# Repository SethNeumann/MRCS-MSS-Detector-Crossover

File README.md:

# Modular Signaling System Crossover board cpOD-M
## License: CERN Open Hardware Licence v1.2

This Barry Draper design conforms to the 
[Modular Signaling System](http://modularsignalsystem.info/index.html)
(MSS) standard, first described by Greg Fuhriman in RMJ in the
1990s, as well as the proposed MSS 2.0 standard.  MSS is widely
used in the Free-mo world, but its also a great solution for a
layout needing basic ABS signaling.  A Crossover board is for a
non-signaled module (detection only).  The MSS Detector Crossover
Board includes a power supply that is fed by the Free-mo Aux Bus
(12 to 14 Volt AC or DCC) and has connectors to communicate with
two adjacent modules and a socket for current detector such as a
[cpOD-M](http://www.modelrailroadcontrolsystems.com/cpod-control-point-occupancy-detector/)
or Dr. Chubb's
[DCCOD](https://www.jlcenterprises.net/products/dcc-optimized-detector).
The MSS Crossover, a cpOD-M, and two straight-through network cables
are all you need to add signal detection to a single track Free-mo
module. (As expected, two of each would be needed for a double track
module.)

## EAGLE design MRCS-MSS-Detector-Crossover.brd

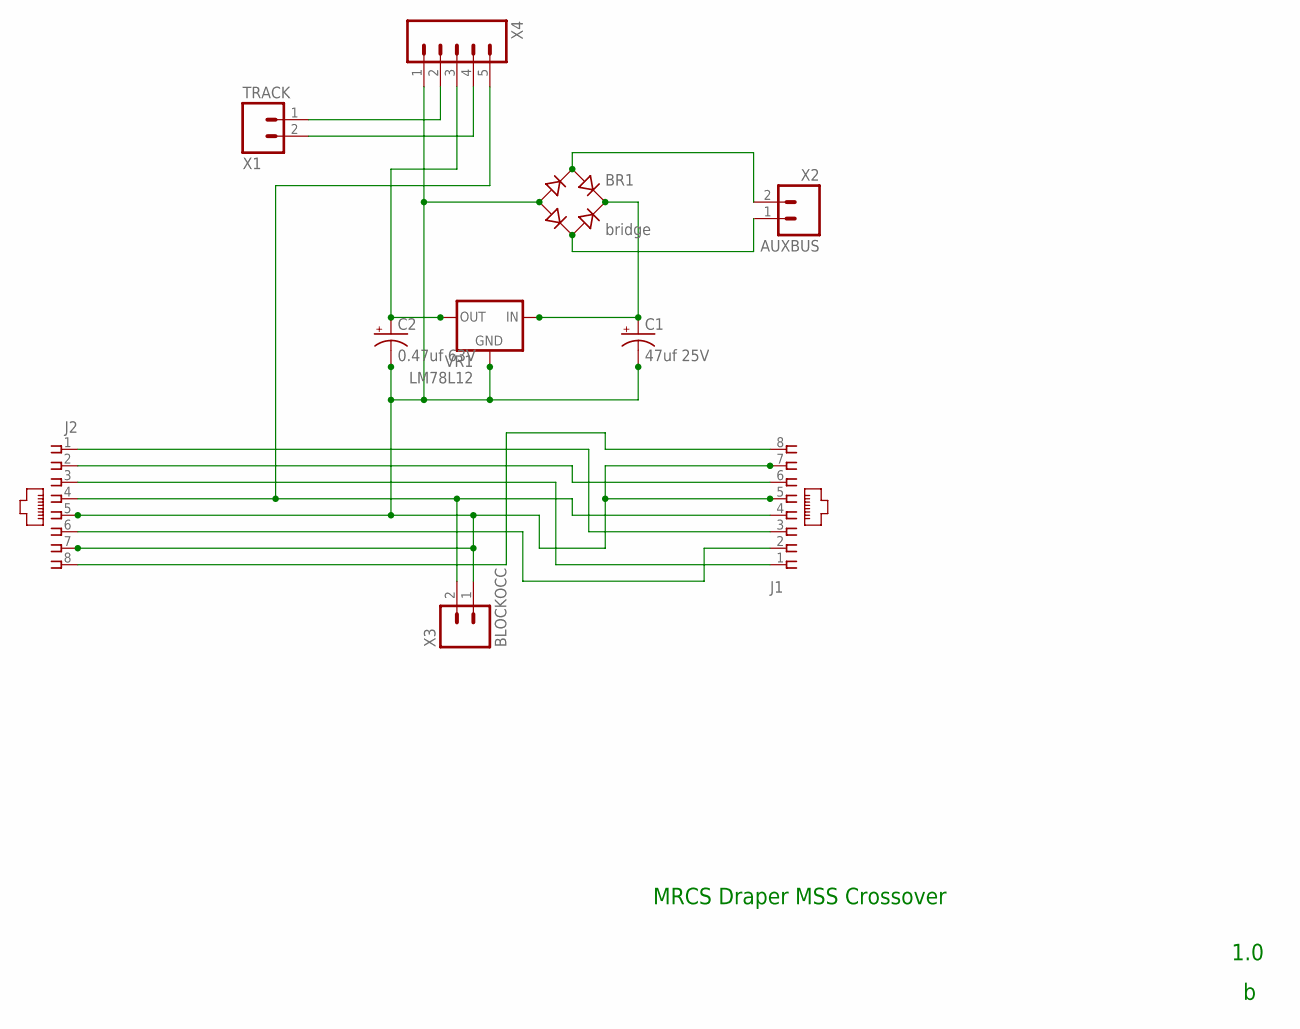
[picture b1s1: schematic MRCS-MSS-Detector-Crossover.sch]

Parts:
BR1: bridge; RB1A
C1: 47uf 25V; E2.5-6
C2: 0.47uf 63V; E2.5-6
J1, J2: CONNECTOR-RJ45-FRONT; RJ45-NO-SHIELD
VR1: LM78L12; TO-92
X1: TRACK; SCREWTERMINAL-5MM-2
X2: AUXBUS; SCREWTERMINAL-5MM-2
X3: BLOCKOCC; SCREWTERMINAL-5MM-2
X4: CONNECTOR-M051.56; KK-156-5

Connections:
AC1: BR1.AC1, X2.2 (B)
AC2: BR1.AC2, X2.1 (A)
GND: BR1.-, C1.-, C2.-, J1.5, J1.7, J2.5, J2.7, VR1.1 (GND), X3.1 (A), X4.1
unnamed: J1.3, J2.1
unnamed: J1.6, J2.2
unnamed: J1.1, J2.3
unnamed: J1.4, J2.4, X3.2 (B), X4.5
unnamed: J1.2, J2.6
unnamed: J1.8, J2.8
TRACK1: X1.1 (A), X4.2
TRACK2: X1.2 (B), X4.4
V12: C2.+, VR1.3 (OUT), X4.3
VIN: BR1.+, C1.+, VR1.2 (IN)

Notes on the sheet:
MRCS Draper MSS Crossover
1.0

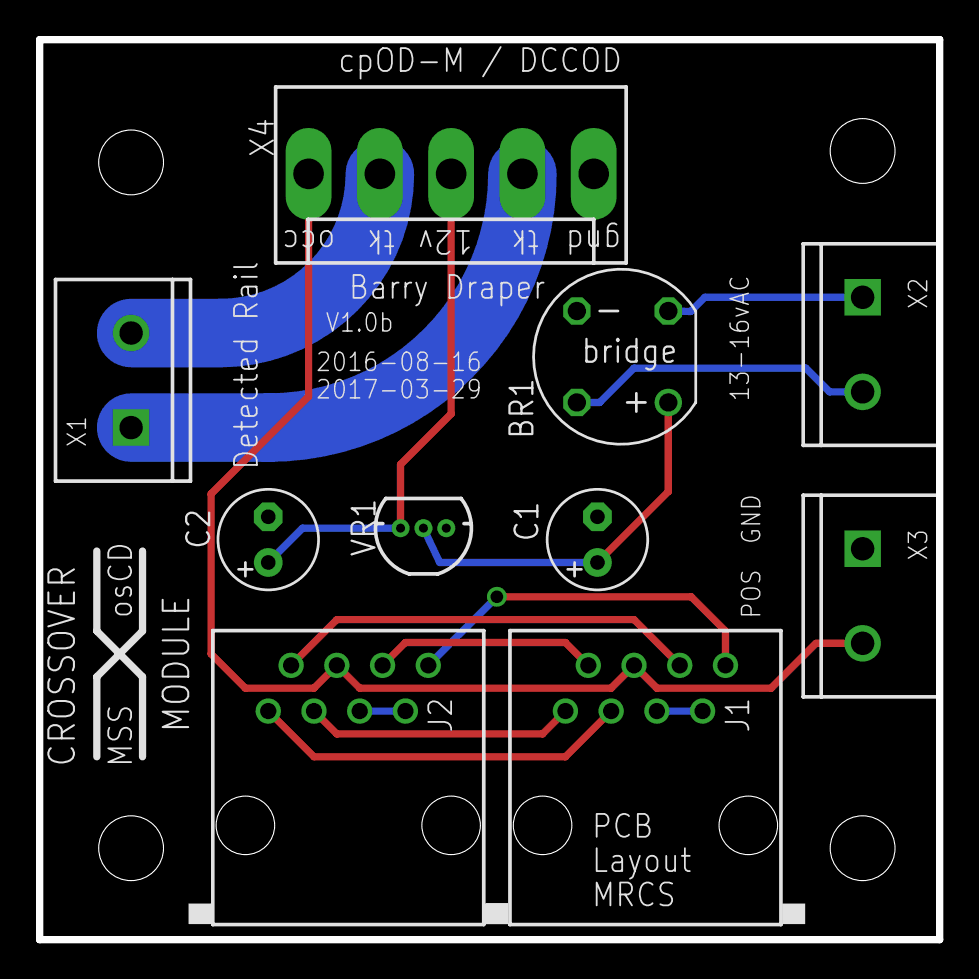
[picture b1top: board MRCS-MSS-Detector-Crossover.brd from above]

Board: 2 copper layers, 50.0 x 50.0 mm, 10 parts (0 on the bottom side), 13 nets.

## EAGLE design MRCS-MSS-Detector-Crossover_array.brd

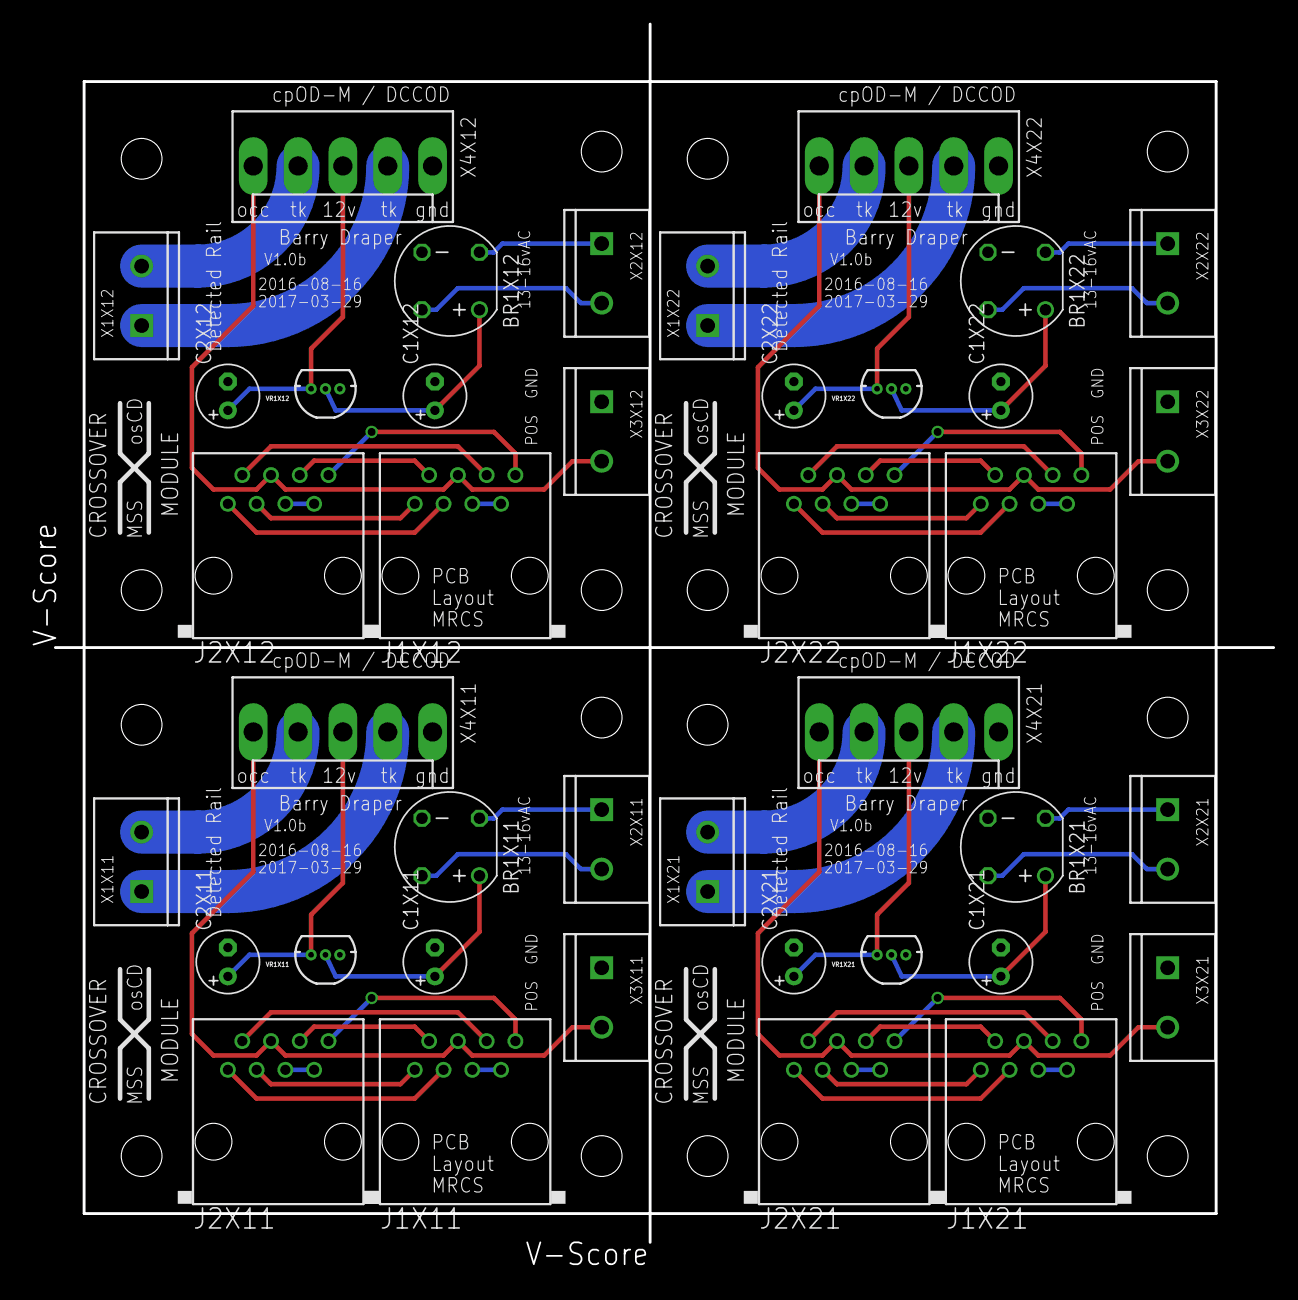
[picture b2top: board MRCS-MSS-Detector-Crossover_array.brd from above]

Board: 2 copper layers, 110.4 x 110.6 mm, 40 parts (0 on the bottom side), 52 nets.

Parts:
BR1X11, BR1X12, BR1X21, BR1X22: RB1A
C1X11, C1X12, C1X21, C1X22, C2X11, C2X12, C2X21, C2X22: E2.5-6
J1X11, J1X12, J1X21, J1X22, J2X11, J2X12, J2X21, J2X22: RJ45-NO-SHIELD
VR1X11, VR1X12, VR1X21, VR1X22: TO-92
X1X11, X1X12, X1X21, X1X22, X2X11, X2X12, X2X21, X2X22, X3X11, X3X12, X3X21, X3X22: SCREWTERMINAL-5MM-2
X4X11, X4X12, X4X21, X4X22: KK-156-5

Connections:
AC1X11: BR1X11.AC1, X2X11.2
AC1X12: BR1X12.AC1, X2X12.2
AC1X21: BR1X21.AC1, X2X21.2
AC1X22: BR1X22.AC1, X2X22.2
AC2X11: BR1X11.AC2, X2X11.1
AC2X12: BR1X12.AC2, X2X12.1
AC2X21: BR1X21.AC2, X2X21.1
AC2X22: BR1X22.AC2, X2X22.1
GNDX11: BR1X11.-, C1X11.-, C2X11.-, J1X11.5, J1X11.7, J2X11.5, J2X11.7, VR1X11.1, X3X11.1, X4X11.1
GNDX12: BR1X12.-, C1X12.-, C2X12.-, J1X12.5, J1X12.7, J2X12.5, J2X12.7, VR1X12.1, X3X12.1, X4X12.1
GNDX21: BR1X21.-, C1X21.-, C2X21.-, J1X21.5, J1X21.7, J2X21.5, J2X21.7, VR1X21.1, X3X21.1, X4X21.1
GNDX22: BR1X22.-, C1X22.-, C2X22.-, J1X22.5, J1X22.7, J2X22.5, J2X22.7, VR1X22.1, X3X22.1, X4X22.1
unnamed: J1X11.3, J2X11.1
unnamed: J1X12.3, J2X12.1
unnamed: J1X21.3, J2X21.1
unnamed: J1X22.3, J2X22.1
unnamed: J1X11.6, J2X11.2
unnamed: J1X12.6, J2X12.2
unnamed: J1X21.6, J2X21.2
unnamed: J1X22.6, J2X22.2
unnamed: J1X11.1, J2X11.3
unnamed: J1X12.1, J2X12.3
unnamed: J1X21.1, J2X21.3
unnamed: J1X22.1, J2X22.3
unnamed: J1X11.4, J2X11.4, X3X11.2, X4X11.5
unnamed: J1X12.4, J2X12.4, X3X12.2, X4X12.5
unnamed: J1X21.4, J2X21.4, X3X21.2, X4X21.5
unnamed: J1X22.4, J2X22.4, X3X22.2, X4X22.5
unnamed: J1X11.2, J2X11.6
unnamed: J1X12.2, J2X12.6
unnamed: J1X21.2, J2X21.6
unnamed: J1X22.2, J2X22.6
unnamed: J1X11.8, J2X11.8
unnamed: J1X12.8, J2X12.8
unnamed: J1X21.8, J2X21.8
unnamed: J1X22.8, J2X22.8
TRACK1X11: X1X11.1, X4X11.2
TRACK1X12: X1X12.1, X4X12.2
TRACK1X21: X1X21.1, X4X21.2
TRACK1X22: X1X22.1, X4X22.2
TRACK2X11: X1X11.2, X4X11.4
TRACK2X12: X1X12.2, X4X12.4
TRACK2X21: X1X21.2, X4X21.4
TRACK2X22: X1X22.2, X4X22.4
V12X11: C2X11.+, VR1X11.3, X4X11.3
V12X12: C2X12.+, VR1X12.3, X4X12.3
V12X21: C2X21.+, VR1X21.3, X4X21.3
V12X22: C2X22.+, VR1X22.3, X4X22.3
VINX11: BR1X11.+, C1X11.+, VR1X11.2
VINX12: BR1X12.+, C1X12.+, VR1X12.2
VINX21: BR1X21.+, C1X21.+, VR1X21.2
VINX22: BR1X22.+, C1X22.+, VR1X22.2

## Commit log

2019-11-28 fix commas in xml
2020-04-23 Moved all components into SPCoast.lbr and panelized
2020-05-04 updated tags
